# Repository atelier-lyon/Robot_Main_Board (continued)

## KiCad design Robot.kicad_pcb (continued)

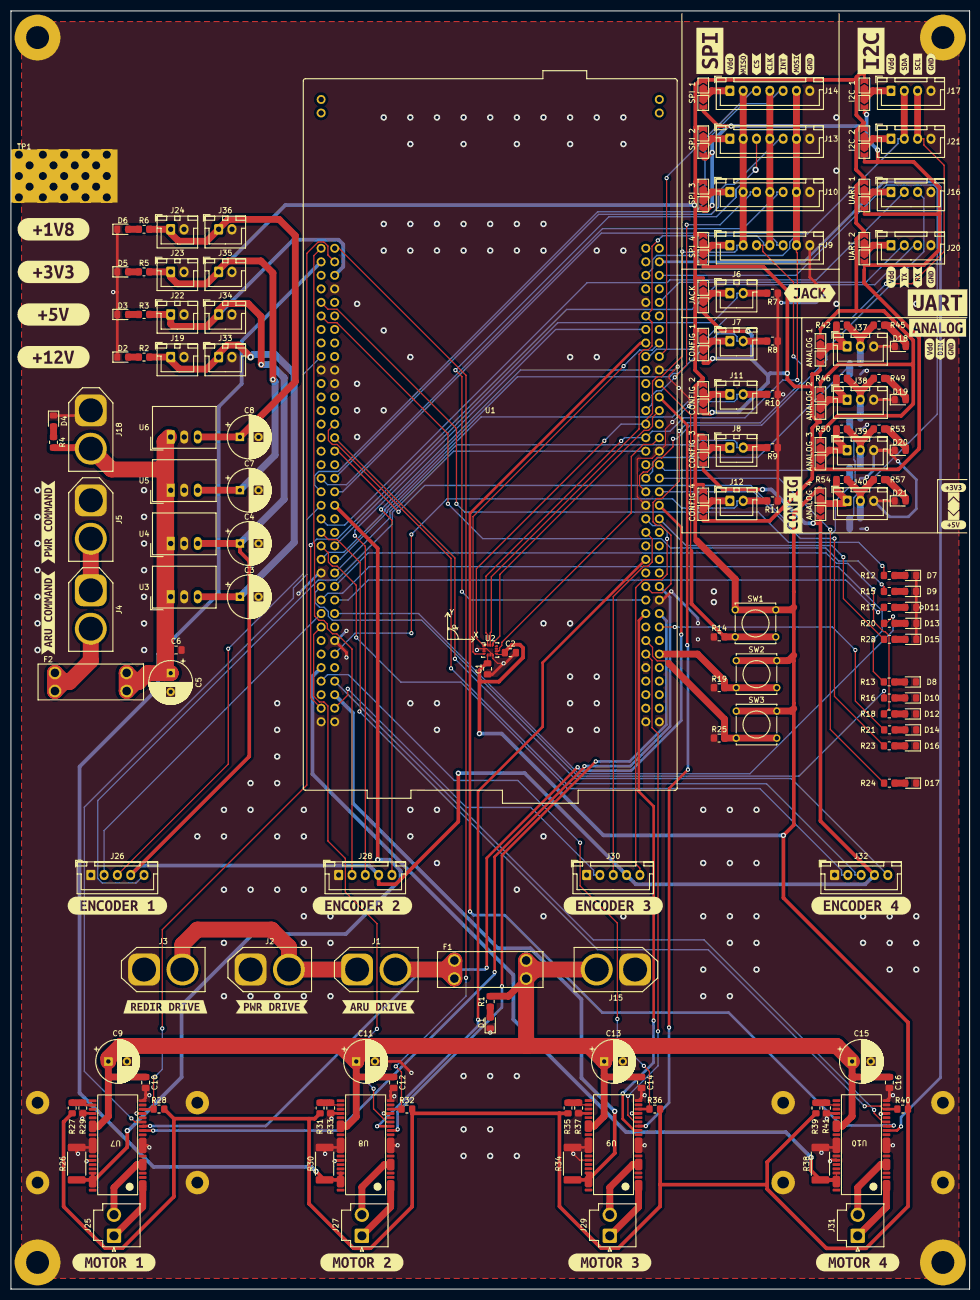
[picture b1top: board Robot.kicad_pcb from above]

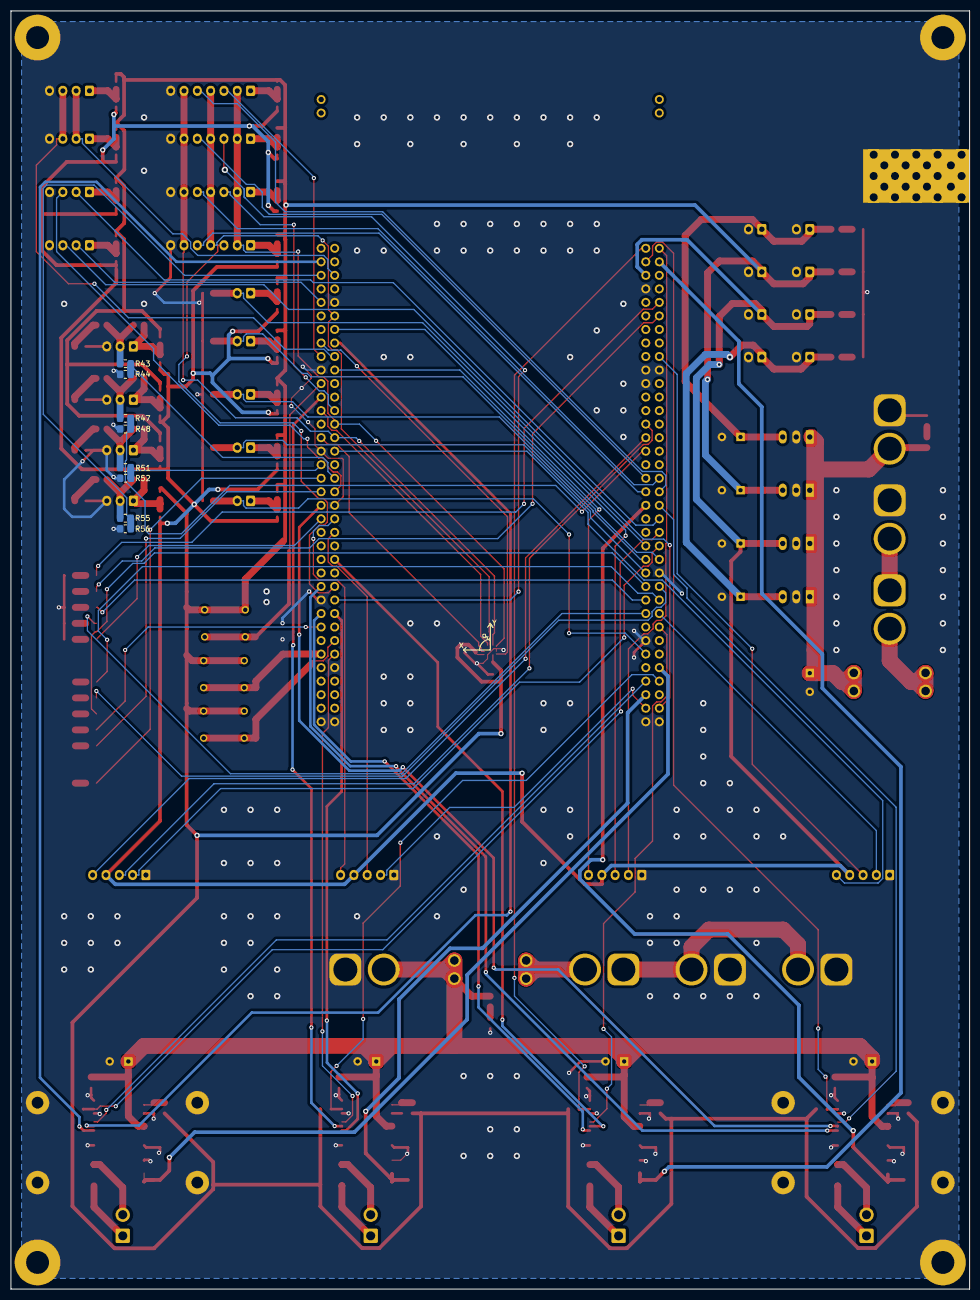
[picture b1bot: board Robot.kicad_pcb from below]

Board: 2 copper layers, 180.0 x 240.0 mm, 239 parts (8 on the bottom side), 140 nets.

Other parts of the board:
kibuzzard-6383A0DF, kibuzzard-6383A0DF#2, kibuzzard-6383A0DF#3, kibuzzard-6383A0DF#4: G***; kibuzzard-6383A0DF
kibuzzard-6383A0ED, kibuzzard-6383A0ED#2, kibuzzard-6383A0ED#3, kibuzzard-6383A0ED#4: G***; kibuzzard-6383A0ED
kibuzzard-6383A1CD: G***; kibuzzard-6383A1CD
kibuzzard-6383A1E2: G***; kibuzzard-6383A1E2
kibuzzard-6383A2E4: G***; kibuzzard-6383A2E4
kibuzzard-6383A04A: G***; kibuzzard-6383A04A
kibuzzard-6383A102: G***; kibuzzard-6383A102
kibuzzard-6383A120: G***; kibuzzard-6383A120
kibuzzard-6383A157: G***; kibuzzard-6383A157
kibuzzard-6383A202: G***; kibuzzard-6383A202
kibuzzard-63847BAC: G***; kibuzzard-63847BAC
kibuzzard-63847BCD: G***; kibuzzard-63847BCD
kibuzzard-63847BE2: G***; kibuzzard-63847BE2
kibuzzard-63847BEA: G***; kibuzzard-63847BEA
kibuzzard-63847C8D: G***; kibuzzard-63847C8D
kibuzzard-63847D2C: G***; kibuzzard-63847D2C
kibuzzard-63847D27: G***; kibuzzard-63847D27
kibuzzard-63847D31: G***; kibuzzard-63847D31
kibuzzard-63847D74: G***; kibuzzard-63847D74
kibuzzard-63847D85: G***; kibuzzard-63847D85
kibuzzard-63847DAA: G***; kibuzzard-63847DAA
kibuzzard-63847DB4: G***; kibuzzard-63847DB4
kibuzzard-63847DDA: G***; kibuzzard-63847DDA
kibuzzard-63847E2F: G***; kibuzzard-63847E2F
kibuzzard-63847E10: G***; kibuzzard-63847E10
kibuzzard-63847E21: G***; kibuzzard-63847E21
kibuzzard-63847E37: G***; kibuzzard-63847E37
kibuzzard-638470A3: G***; kibuzzard-638470A3
kibuzzard-638476CA: G***; kibuzzard-638476CA
kibuzzard-6384717F: G***; kibuzzard-6384717F
kibuzzard-6384784C: G***; kibuzzard-6384784C
kibuzzard-6384788E: G***; kibuzzard-6384788E
kibuzzard-6384799C: G***; kibuzzard-6384799C
kibuzzard-63847057: G***; kibuzzard-63847057
kibuzzard-63847094: G***; kibuzzard-63847094
kibuzzard-63847925: G***; kibuzzard-63847925
kibuzzard-63847930: G***; kibuzzard-63847930

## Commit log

2023-01-23 [ROOT] Initial commit
2023-01-23 [PRO] Add Project
2023-01-23 [SCH] Add Schematics
2023-01-23 [PCB] Add PCB
2023-01-23 [EXPORT] Update export
2023-01-23 [VIEW] Add Views
2023-01-23 [ROOT] Fix README
